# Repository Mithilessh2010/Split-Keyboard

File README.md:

# Split Keyboard

**Split Keyboard** is a 60-key split mechanical keyboard with wireless support. It runs on a XIAO nRF52840 and is powered by a battery, allowing it to connect to a computer using Bluetooth.

I made this project to learn more about CAD, PCB design, and firmware. I also wanted to build something useful that I can use every day since I currently just use a laptop keyboard.

---

## Overview

This keyboard is split into two halves for better ergonomics. Each half has its own PCB, and all available GPIO pins on the microcontroller are used for the key matrix.

The firmware is written using CircuitPython and the KMK library. Right now, only the right half is programmed, and wireless communication between both halves is still in progress.

---

## CAD Design

All parts were designed in Fusion 360. This project helped me learn how to use curves and improve my overall CAD skills.

After designing the parts, I exported them into Blender to create realistic renders of the keyboard. I also used PCB STEP files, which made it much easier to design the case accurately around the electronics.

---

## PCB Design

The PCBs were designed using KiCad. The keyboard uses a standard switch matrix along with diodes for each key.

There are also test points on the PCB that connect to battery power and ground, which can be useful for debugging and testing.

---

## Firmware

The firmware is built using CircuitPython with the KMK library.

At the moment:
- Only the right side of the keyboard is working
- Wireless support has not been fully implemented yet
- More testing will be done once the PCBs arrive

The firmware will be updated as I test and improve the keyboard in real life.

---

## Keymap

The current keymap is designed for the right half of the keyboard. It will likely change as I continue testing and improving usability.

---

## Bill of Materials (BOM)

| Name                                   | Purpose                                      | Quantity | Total Cost (USD) |
|----------------------------------------|----------------------------------------------|----------|------------------|
| LiPo Battery                           | To power the system                          | 1        | 10.66            |
| MINI NRF52840 Development Board        | Main microcontroller (brain)                 | 2        | 8.72             |
| Keycap Set                             | Keycaps for the switches                     | 1        | 21.07            |
| GATERON G Pro Milk Yellow Switches     | Mechanical switches for keys                 | 1        | 20.20            |
| 1N4148 Diodes                          | Used in the keyboard matrix                  | 1        | 2.46             |
| M3 Heat-Set Inserts (4mm, 4.2mm OD)    | Used to secure the case with screws          | 1        | 12.65            |
| PCB                                    | Custom printed circuit board                 | 1        | 30.84            |
| Tax                                    | Sales tax                                   | —        | 8.65             |
| Shipping                               | Shipping costs                              | —        | 8.72             |
|                                        |                                              |          | **Total: $123.97** |

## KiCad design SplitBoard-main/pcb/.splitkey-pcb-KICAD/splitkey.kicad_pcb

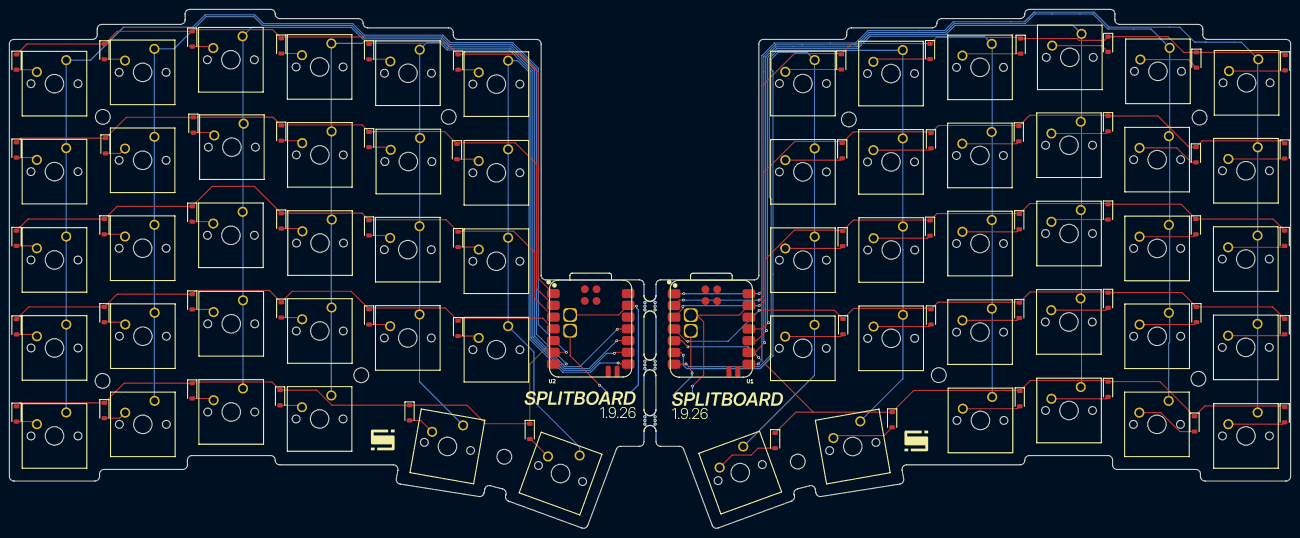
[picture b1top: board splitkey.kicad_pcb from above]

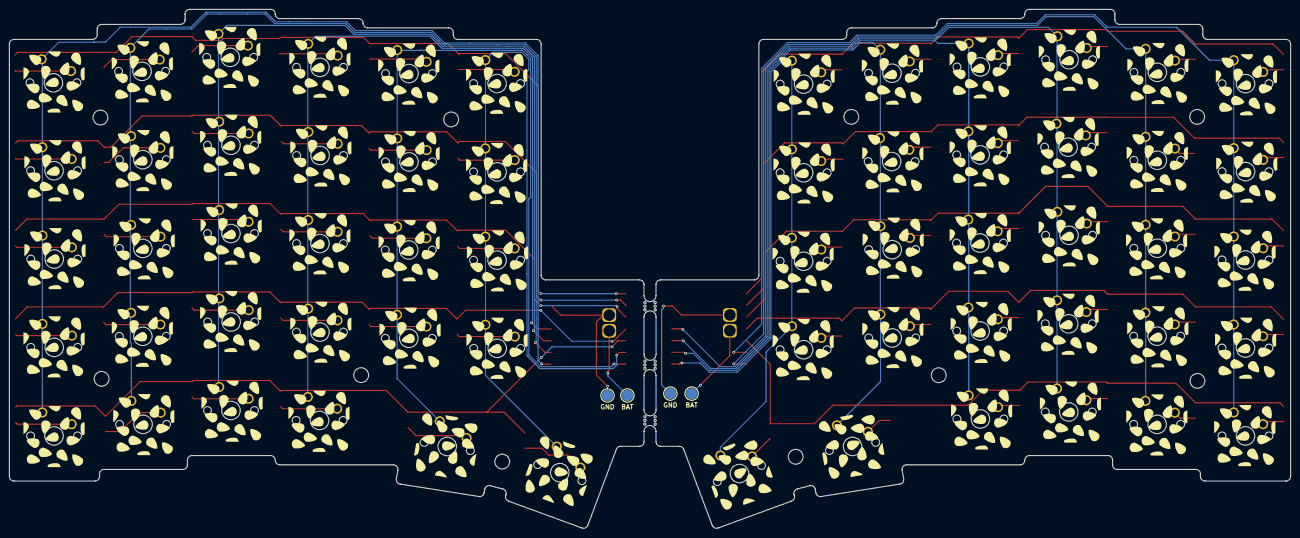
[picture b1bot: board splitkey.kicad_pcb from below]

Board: 2 copper layers, 277.1 x 112.2 mm, 139 parts (4 on the bottom side), 85 nets.

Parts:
BO1, BO2, BO3: BreakOff; mouse-bite-2.54mm-slot
D32, D33, D34, D35, D36, D37, D38, D39, D40, D41, D42, D43, D44, D45, D46, D47, D48, D49, D50, D51, D52, D53, D54, D55, D56, D57, D58, D59, D60, D61, D91, D92, D93, D94, D95, D96, D97, D98, D99, D100, D101, D102, D103, D104, D105, D106, D107, D108, D109, D110, D111, D112, D113, D114, D115, D116, D117, D118, D119, D120: D; D_SOD-123
H1, H2, H3, H4, H5, H6, H7, H8, H9, H11: MountingHole; MountingHole_3.2mm_M3
SW1, SW2, SW3, SW4, SW5, SW6, SW7, SW8, SW9, SW10, SW11, SW12, SW13, SW14, SW15, SW16, SW17, SW18, SW19, SW20, SW21, SW22, SW23, SW24, SW25, SW26, SW27, SW28, SW29, SW30, SW31, SW32, SW33, SW34, SW35, SW36, SW37, SW38, SW39, SW40, SW41, SW42, SW43, SW44, SW45, SW46, SW47, SW48, SW49, SW50, SW51, SW52, SW53, SW54, SW55, SW56, SW57, SW58, SW59, SW60: SW_Push; SW_Cherry_MX_1.00u_PCB
TP1, TP3: BAT; TestPoint_Pad_D2.5mm
TP2, TP4: GND; TestPoint_Pad_D2.5mm
U1, U2: XIAO-nRF52840-SMD; modified-XIAO-nRF52840-SMD

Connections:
/left/Col0: SW1.1, SW2.1, SW3.1, SW4.1, SW5.1, U1.6 (P0.05_A5_D5_SCL)
/left/Col1: SW6.1, SW7.1, SW8.1, SW9.1, SW10.1, U1.7 (P1.11_D6_TX)
/left/Col2: SW11.1, SW12.1, SW13.1, SW14.1, SW15.1, U1.11 (P1.15_D10_MOSI)
/left/Col3: SW16.1, SW17.1, SW18.1, SW19.1, SW20.1, U1.10 (P1.14_D9_MISO)
/left/Col4: SW21.1, SW22.1, SW23.1, SW24.1, SW25.1, U1.9 (P1.13_D8_SCK)
/left/Col5: SW26.1, SW27.1, SW28.1, SW29.1, SW30.1, U1.8 (P1.12_D7_RX)
/left/Row0: D32.1 (K), D37.1 (K), D42.1 (K), D47.1 (K), D52.1 (K), D57.1 (K), U1.1 (P0.02_A0_D0)
/left/Row1: D33.1 (K), D38.1 (K), D43.1 (K), D48.1 (K), D53.1 (K), D58.1 (K), U1.2 (P0.03_A1_D1)
/left/Row2: D34.1 (K), D39.1 (K), D44.1 (K), D49.1 (K), D54.1 (K), D59.1 (K), U1.3 (P0.28_A2_D2)
/left/Row3: D35.1 (K), D40.1 (K), D45.1 (K), D50.1 (K), D55.1 (K), D60.1 (K), U1.4 (P0.29_A3_D3)
/left/Row4: D36.1 (K), D41.1 (K), D46.1 (K), D51.1 (K), D56.1 (K), D61.1 (K), U1.5 (P0.04_A4_D4_SDA)
/left/VBAT: TP3.1, U1.15 (BAT)
/right/Col0: SW31.1, SW32.1, SW33.1, SW34.1, SW35.1, U2.6 (P0.05_A5_D5_SCL)
/right/Col1: SW36.1, SW37.1, SW38.1, SW39.1, SW40.1, U2.7 (P1.11_D6_TX)
/right/Col2: SW41.1, SW42.1, SW43.1, SW44.1, SW45.1, U2.11 (P1.15_D10_MOSI)
/right/Col3: SW46.1, SW47.1, SW48.1, SW49.1, SW50.1, U2.10 (P1.14_D9_MISO)
/right/Col4: SW51.1, SW52.1, SW53.1, SW54.1, SW55.1, U2.9 (P1.13_D8_SCK)
/right/Col5: SW56.1, SW57.1, SW58.1, SW59.1, SW60.1, U2.8 (P1.12_D7_RX)
/right/Row0: D91.1 (K), D96.1 (K), D101.1 (K), D106.1 (K), D111.1 (K), D116.1 (K), U2.1 (P0.02_A0_D0)
/right/Row1: D92.1 (K), D97.1 (K), D102.1 (K), D107.1 (K), D112.1 (K), D117.1 (K), U2.2 (P0.03_A1_D1)
/right/Row2: D93.1 (K), D98.1 (K), D103.1 (K), D108.1 (K), D113.1 (K), D118.1 (K), U2.3 (P0.28_A2_D2)
/right/Row3: D94.1 (K), D99.1 (K), D104.1 (K), D109.1 (K), D114.1 (K), D119.1 (K), U2.4 (P0.29_A3_D3)
/right/Row4: D95.1 (K), D100.1 (K), D105.1 (K), D110.1 (K), D115.1 (K), D120.1 (K), U2.5 (P0.04_A4_D4_SDA)
/right/VBAT: TP1.1, U2.15 (BAT)
GND: TP2.1, TP4.1, U1.13 (GND), U1.16 (GND), U2.13 (GND), U2.16 (GND)
unnamed: D32.2 (A), SW1.2
unnamed: D33.2 (A), SW2.2
unnamed: D34.2 (A), SW3.2
unnamed: D35.2 (A), SW4.2
unnamed: D36.2 (A), SW5.2
unnamed: D37.2 (A), SW6.2
unnamed: D38.2 (A), SW7.2
unnamed: D39.2 (A), SW8.2
unnamed: D40.2 (A), SW9.2
unnamed: D41.2 (A), SW10.2
unnamed: D42.2 (A), SW11.2
unnamed: D43.2 (A), SW12.2
unnamed: D44.2 (A), SW13.2
unnamed: D45.2 (A), SW14.2
unnamed: D46.2 (A), SW15.2
unnamed: D47.2 (A), SW16.2
unnamed: D48.2 (A), SW17.2
unnamed: D49.2 (A), SW18.2
unnamed: D50.2 (A), SW19.2
unnamed: D51.2 (A), SW20.2
unnamed: D52.2 (A), SW21.2
unnamed: D53.2 (A), SW22.2
unnamed: D54.2 (A), SW23.2
unnamed: D55.2 (A), SW24.2
unnamed: D56.2 (A), SW25.2
unnamed: D57.2 (A), SW26.2
unnamed: D58.2 (A), SW27.2
unnamed: D59.2 (A), SW28.2
unnamed: D60.2 (A), SW29.2
unnamed: D61.2 (A), SW30.2
unnamed: D91.2 (A), SW31.2
unnamed: D92.2 (A), SW32.2
unnamed: D93.2 (A), SW33.2
unnamed: D94.2 (A), SW34.2
unnamed: D95.2 (A), SW35.2
unnamed: D96.2 (A), SW36.2
unnamed: D97.2 (A), SW37.2
unnamed: D98.2 (A), SW38.2
unnamed: D99.2 (A), SW39.2
unnamed: D100.2 (A), SW40.2
unnamed: D101.2 (A), SW41.2
unnamed: D102.2 (A), SW42.2
unnamed: D103.2 (A), SW43.2
unnamed: D104.2 (A), SW44.2
unnamed: D105.2 (A), SW45.2
unnamed: D106.2 (A), SW46.2
unnamed: D107.2 (A), SW47.2
unnamed: D108.2 (A), SW48.2
unnamed: D109.2 (A), SW49.2
unnamed: D110.2 (A), SW50.2
unnamed: D111.2 (A), SW51.2
unnamed: D112.2 (A), SW52.2
unnamed: D113.2 (A), SW53.2
unnamed: D114.2 (A), SW54.2
unnamed: D115.2 (A), SW55.2
unnamed: D116.2 (A), SW56.2
unnamed: D117.2 (A), SW57.2
unnamed: D118.2 (A), SW58.2
unnamed: D119.2 (A), SW59.2
unnamed: D120.2 (A), SW60.2

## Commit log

2026-04-06 All the stuff
2026-04-06 Fixed Folders
2026-04-06 new bom
2026-04-06 Add README with project details for Split Keyboard
    Added detailed project information including overview, CAD design, PCB design, firmware, keymap, and bill of materials.
